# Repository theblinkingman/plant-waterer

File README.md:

# plant-waterer
TDR sensor to water a plant automatically

See https://hackaday.io/project/193184-tdr-soil-moisture-sensor for more details

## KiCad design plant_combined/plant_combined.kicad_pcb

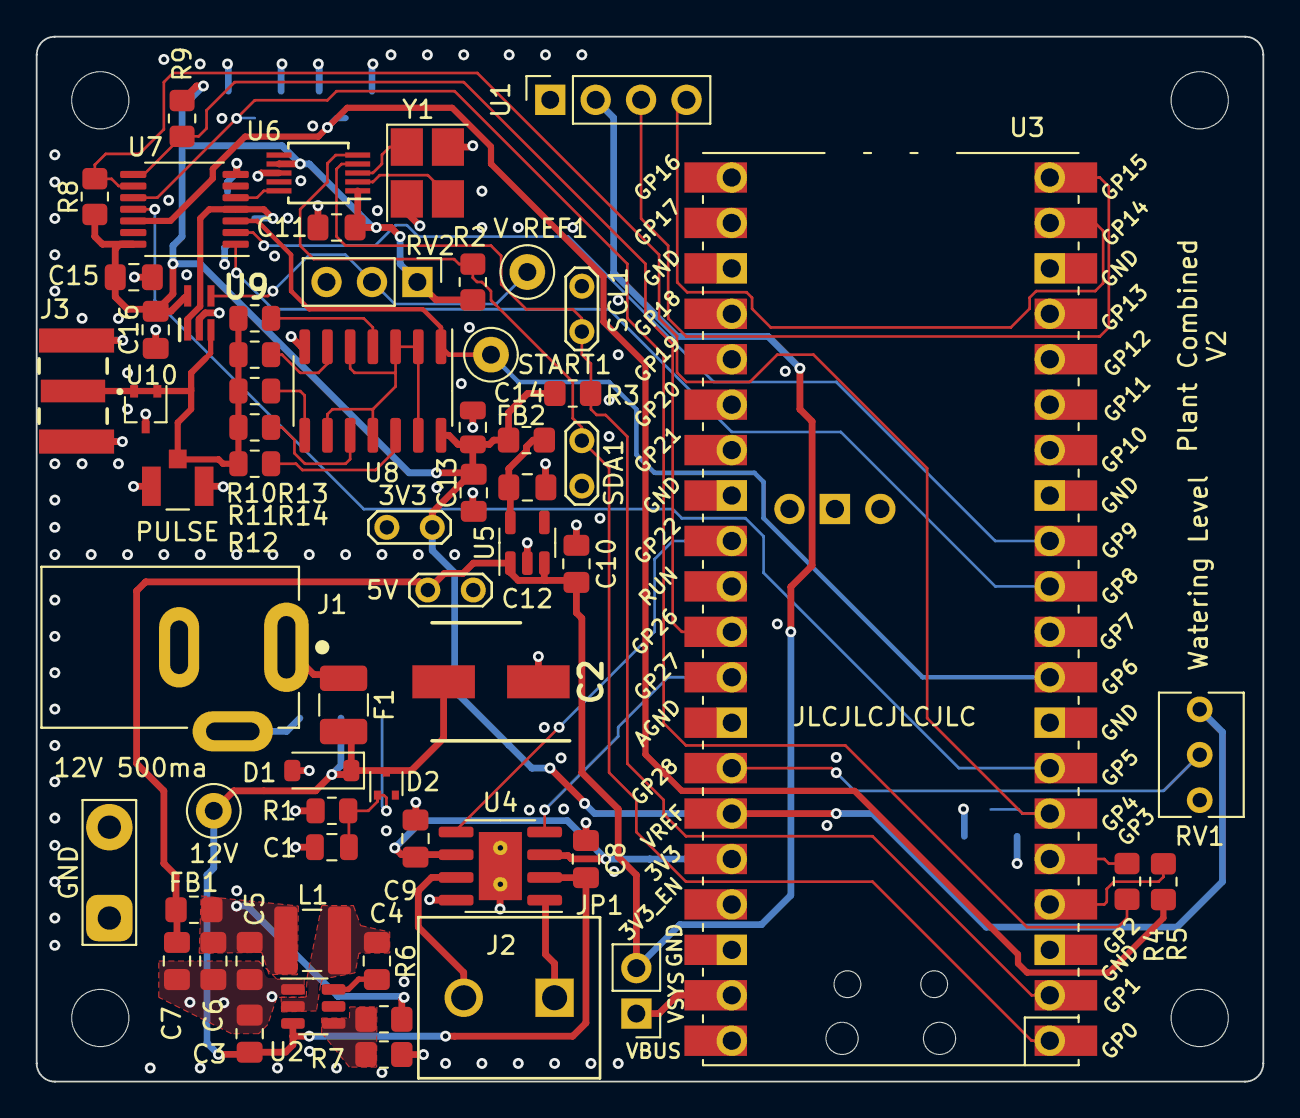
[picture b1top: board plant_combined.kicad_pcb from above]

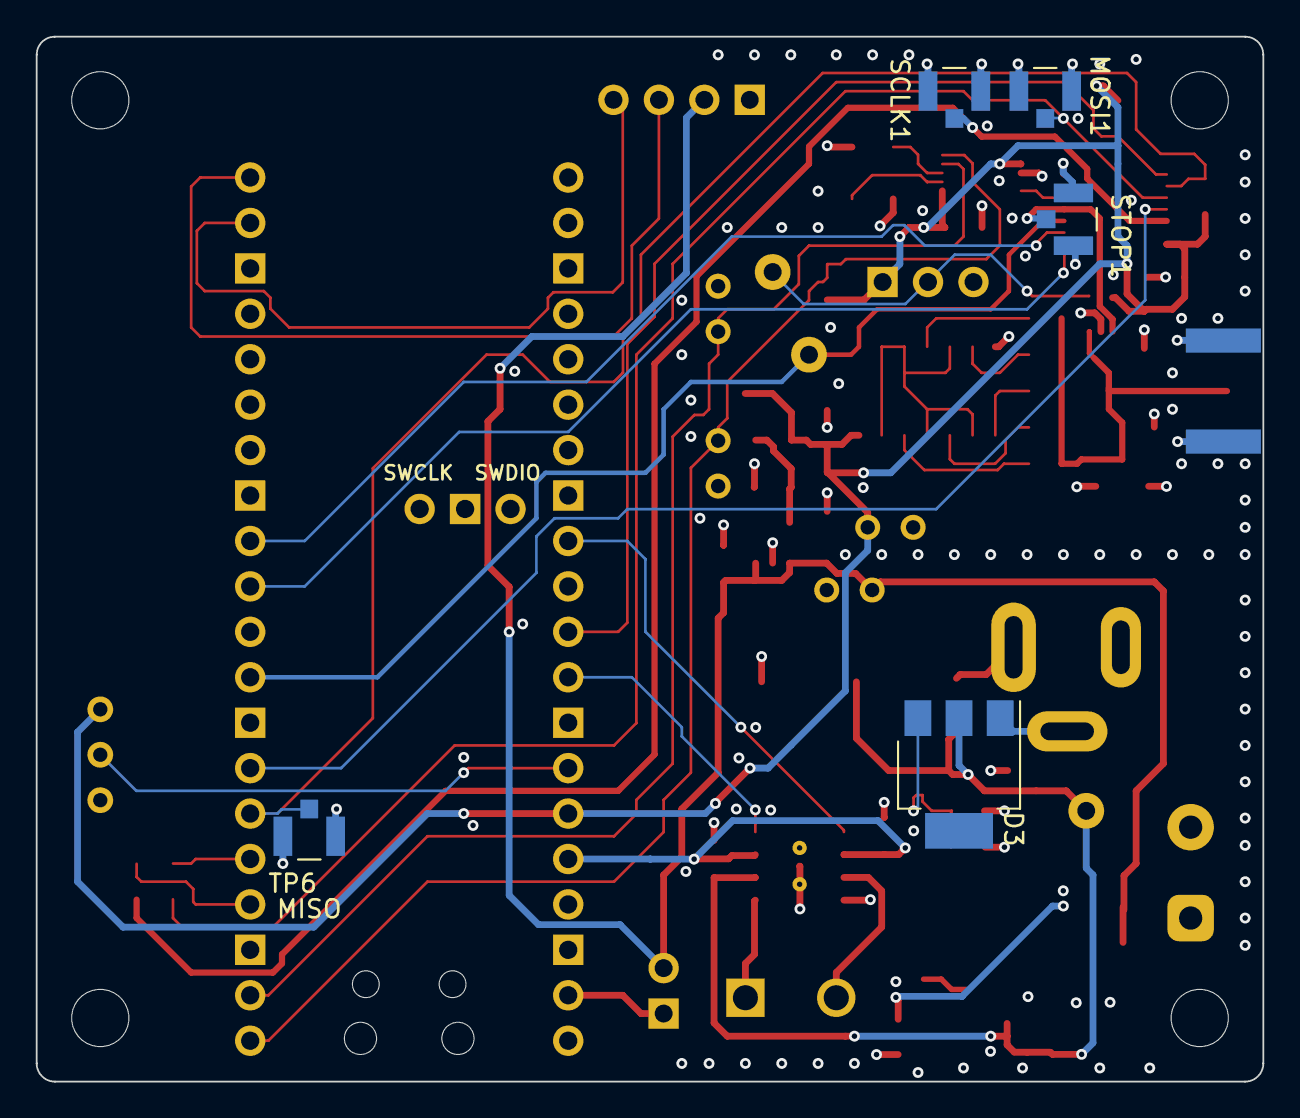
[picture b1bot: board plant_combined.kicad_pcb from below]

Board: 4 copper layers, 68.6 x 58.4 mm, 67 parts (5 on the bottom side), 44 nets.

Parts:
C1: 10nf; C_0805_2012Metric
C2: 100uF; UUA1C101MCL1GS
C3, C8: 10uF; C_0805_2012Metric_Pad1.18x1.45mm_HandSolder
C4: 100nF; C_0805_2012Metric_Pad1.18x1.45mm_HandSolder
C5: 22uF; C_0805_2012Metric_Pad1.18x1.45mm_HandSolder
C6, C7, C9, C10, C11, C12, C13, C15, C16: 1uF; C_0805_2012Metric_Pad1.18x1.45mm_HandSolder
C14: 1uF; C_0805_2012Metric
D1: TV02W480-G; D_SOD-123
D2: BZX84Cxx; SOT-523
D3: BT168GW; SOT-223
F1: 500ma; Fuse_1210_3225Metric_Pad1.42x2.65mm_HandSolder
FB1, FB2: ACML-0805-601-T; R_0805_2012Metric_Pad1.20x1.40mm_HandSolder
J1: PJ-002AH; CUI_PJ-002AH
J2: Conn_01x02; CONN 1x2 5mm
J3: SMA-J-P-H-ST-EM1; SAMTEC_SMA-J-P-H-ST-EM1
JP1: Jumper_2_Bridged; PinHeader_1x02_P2.54mm_Vertical
L1: 4.7uH; SDCL1V4020
MOSI1: TestPoint; HIROSE_U.FL-R-SMT-1(01)
R1: 68; R_0805_2012Metric
R2, R3: 4K7; R_0805_2012Metric_Pad1.20x1.40mm_HandSolder
R4, R5: 82; R_0805_2012Metric_Pad1.20x1.40mm_HandSolder
R6: 52K3; R_0805_2012Metric_Pad1.20x1.40mm_HandSolder
R7, R9: 10K; R_0805_2012Metric_Pad1.20x1.40mm_HandSolder
R8: 1K; R_0805_2012Metric_Pad1.20x1.40mm_HandSolder
R10, R11, R12, R13, R14: 249; R_0805_2012Metric
RV1: R_Potentiometer; Potentiometer_Bourns_3266Y_Vertical
RV2: 10K; PinHeader_1x03_P2.54mm_Vertical
SCL1: TestPoint_2Pole; TestPoint_2Pads_Pitch2.54mm_Drill1mm
SCLK1: TestPoint; HIROSE_U.FL-R-SMT-1(01)
SDA1: TestPoint_2Pole; TestPoint_2Pads_Pitch2.54mm_Drill1mm
START1: TestPoint; TestPoint_Loop_D1.80mm_Drill1.0mm_Beaded
STOP1: TestPoint; HIROSE_U.FL-R-SMT-1(01)
TP1: TestPoint; TestPoint_Loop_D1.80mm_Drill1.0mm_Beaded
TP1#2, TP6: TestPoint; HIROSE_U.FL-R-SMT-1(01)
TP2: TestPoint_2Pole; TestPoint_2Pads_Pitch5.08mm_Drill1.3mm
TP3: TestPoint; TestPoint_2Pads_Pitch2.54mm_Drill1mm
TP4: TestPoint_2Pole; TestPoint_2Pads_Pitch2.54mm_Drill1mm
U1: OLED_DISP; PinSocket_1x04_P2.54mm_Vertical
U2: AP62200WU-7; SOT-23-6
U3: PicoW; RPi_PicoW_SMD_TH
U4: ZXBM5210-SP-13; SOIC-8-1EP_3.9x4.9mm_P1.27mm_EP2.41x3.81mm
U5: MCP1700T; TSOT-23-5
U6: SI5351A-B-GT; MSOP-10_3x3mm_P0.5mm
U7: TDC7200PWR; TSSOP-14_4.4x5mm_P0.65mm
U8: 74AC14SC; SOIC-14_3.9x8.7mm_P1.27mm
U9: ADCMP600BKSZ-R2; SOT65P210X110-5N
U10: ESD7002; SOT-323_SC-70
V REF1: TestPoint; TestPoint_Loop_D1.80mm_Drill1.0mm_Beaded
Y1: Crystal_GND24; Crystal_SMD_3225-4Pin_3.2x2.5mm_HandSoldering

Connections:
+3.3V: C9.2, U3.36 (3V3), U4.3 (VDD), U4.6 (VREF)
+3.3VA: C11.2, C13.2, C14.1, C15.2, C16.2, FB2.2, R2.1, R3.1, R8.2, R9.2, RV1.1, RV2.1, TP4.2, U3.35 (ADC_VREF), U6.1 (VDD), U6.7 (VDDO), U7.14 (VDD), U8.14 (VCC), U9.5 (VCC_I/O)
+5V: C7.2, C10.2, FB1.2, JP1.2 (B), TP3.2, U1.2 (VCC), U5.1 (IN), U5.3 (EN)
+12P: C2.2, C3.2, C8.2, D1.1, D2.3 (K), D3.2 (A), F1.2, TP1.1, U2.3 (VIN), U4.2 (VM)
/5V_JUMP: JP1.1 (A), U3.39 (VSYS)
/5V_UNFILT: C5.2, C6.2, FB1.1, L1.2, R6.1
/AIN1: U3.32 (GPIO27_ADC1), U4.4 (FWD)
/AIN2: U3.29 (GPIO22), U4.5 (REV)
/AO1: J2.1, U4.1 (OUT_1)
/AO2: J2.2, U4.7 (OUT_2)
/FB: R6.2, R7.1, U2.4 (FB)
/SW: C4.1, L1.1, U2.2 (SW)
/VIN: F1.1, J1.1
/tdr_sensor/+3_UNFILTERED: C12.2, FB2.1, U5.5 (OUT)
/tdr_sensor/CLK: U6.10 (CLK0), U7.5 (CLOCK)
/tdr_sensor/PULSE: J3.1, R10.2, R11.2, R12.2, R13.2, R14.2, TP1#2.1, U9.3 (VP), U10.1, U10.2
/tdr_sensor/STOP: STOP1.1, U7.4 (STOP), U9.1 (Q)
/tdr_sensor/V ref: RV2.2, U9.4 (VN), V REF1.1
EN: U3.11 (GPIO8), U7.1 (ENABLE)
GND: C1.2, C2.1, C3.1, C5.1, C6.1, C7.1, C8.1, C9.1, C10.1, C11.1, C12.1, C13.1, C14.2, C15.1, C16.1, D1.2, D3.1 (K), J1.2, J1.3, J3.2_1, J3.2_2, J3.3_1, J3.3_2, MOSI1.2, R1.1, R7.2, RV1.3, RV2.3, SCL1.2, SCLK1.2, SDA1.1, STOP1.2, TP1#2.2, TP2.1, TP2.2, TP3.1, TP4.1, TP6.2, U1.1 (GND), U2.1 (GND), U3.3 (GND), U3.8 (GND), U3.13 (GND), U3.18 (GND), U3.23 (GND), U3.28 (GND), U3.33 (AGND), U3.38 (GND), U4.8 (GND), U4.9 (EP), U5.2 (GND), U6.8 (GND), U7.7 (GND), U8.7 (GND), U9.2 (GND), U10.3, Y1.2, Y1.4
INTB: R9.1, U3.31 (GPIO26_ADC0), U7.8 (INTB)
MISO: R8.1, TP6.1, U3.6 (GPIO4), U7.9 (DOUT)
MOSI: MOSI1.1, R4.2, U7.10 (DIN)
unnamed: C1.1, D2.1 (A), D3.3 (G), R1.2
unnamed: U1.3 (SCK), U3.20 (GPIO15)
unnamed: U1.4 (SDA), U3.19 (GPIO14)
unnamed: C4.2, U2.6 (BST)
unnamed: R5.1, U3.4 (GPIO2)
unnamed: R4.1, U3.5 (GPIO3)
unnamed: RV1.2, U3.34 (GPIO28_ADC2)
unnamed: U6.2 (XA), Y1.3
unnamed: U6.3 (XB), Y1.1
unnamed: U8.2 (O0), U8.3 (I1), U8.5 (I2), U8.9 (I3), U8.11 (I4), U8.13 (I5)
unnamed: R10.1, U8.4 (O1)
unnamed: R11.1, U8.6 (O2)
unnamed: R12.1, U8.8 (O3)
unnamed: R13.1, U8.10 (O4)
unnamed: R14.1, U8.12 (O5)
SCL: R3.2, SCL1.1, U3.2 (GPIO1), U6.4 (SCL)
SCLK: R5.2, SCLK1.1, U7.12 (SCLK)
SDA: R2.2, SDA1.2, U3.1 (GPIO0), U6.5 (SDA)
START: START1.1, U3.9 (GPIO6), U7.3 (START), U8.1 (I0)
TDC CSB: U3.7 (GPIO5), U7.11 (CSB)
TRIG: U3.12 (GPIO9), U7.2 (TRIGG)

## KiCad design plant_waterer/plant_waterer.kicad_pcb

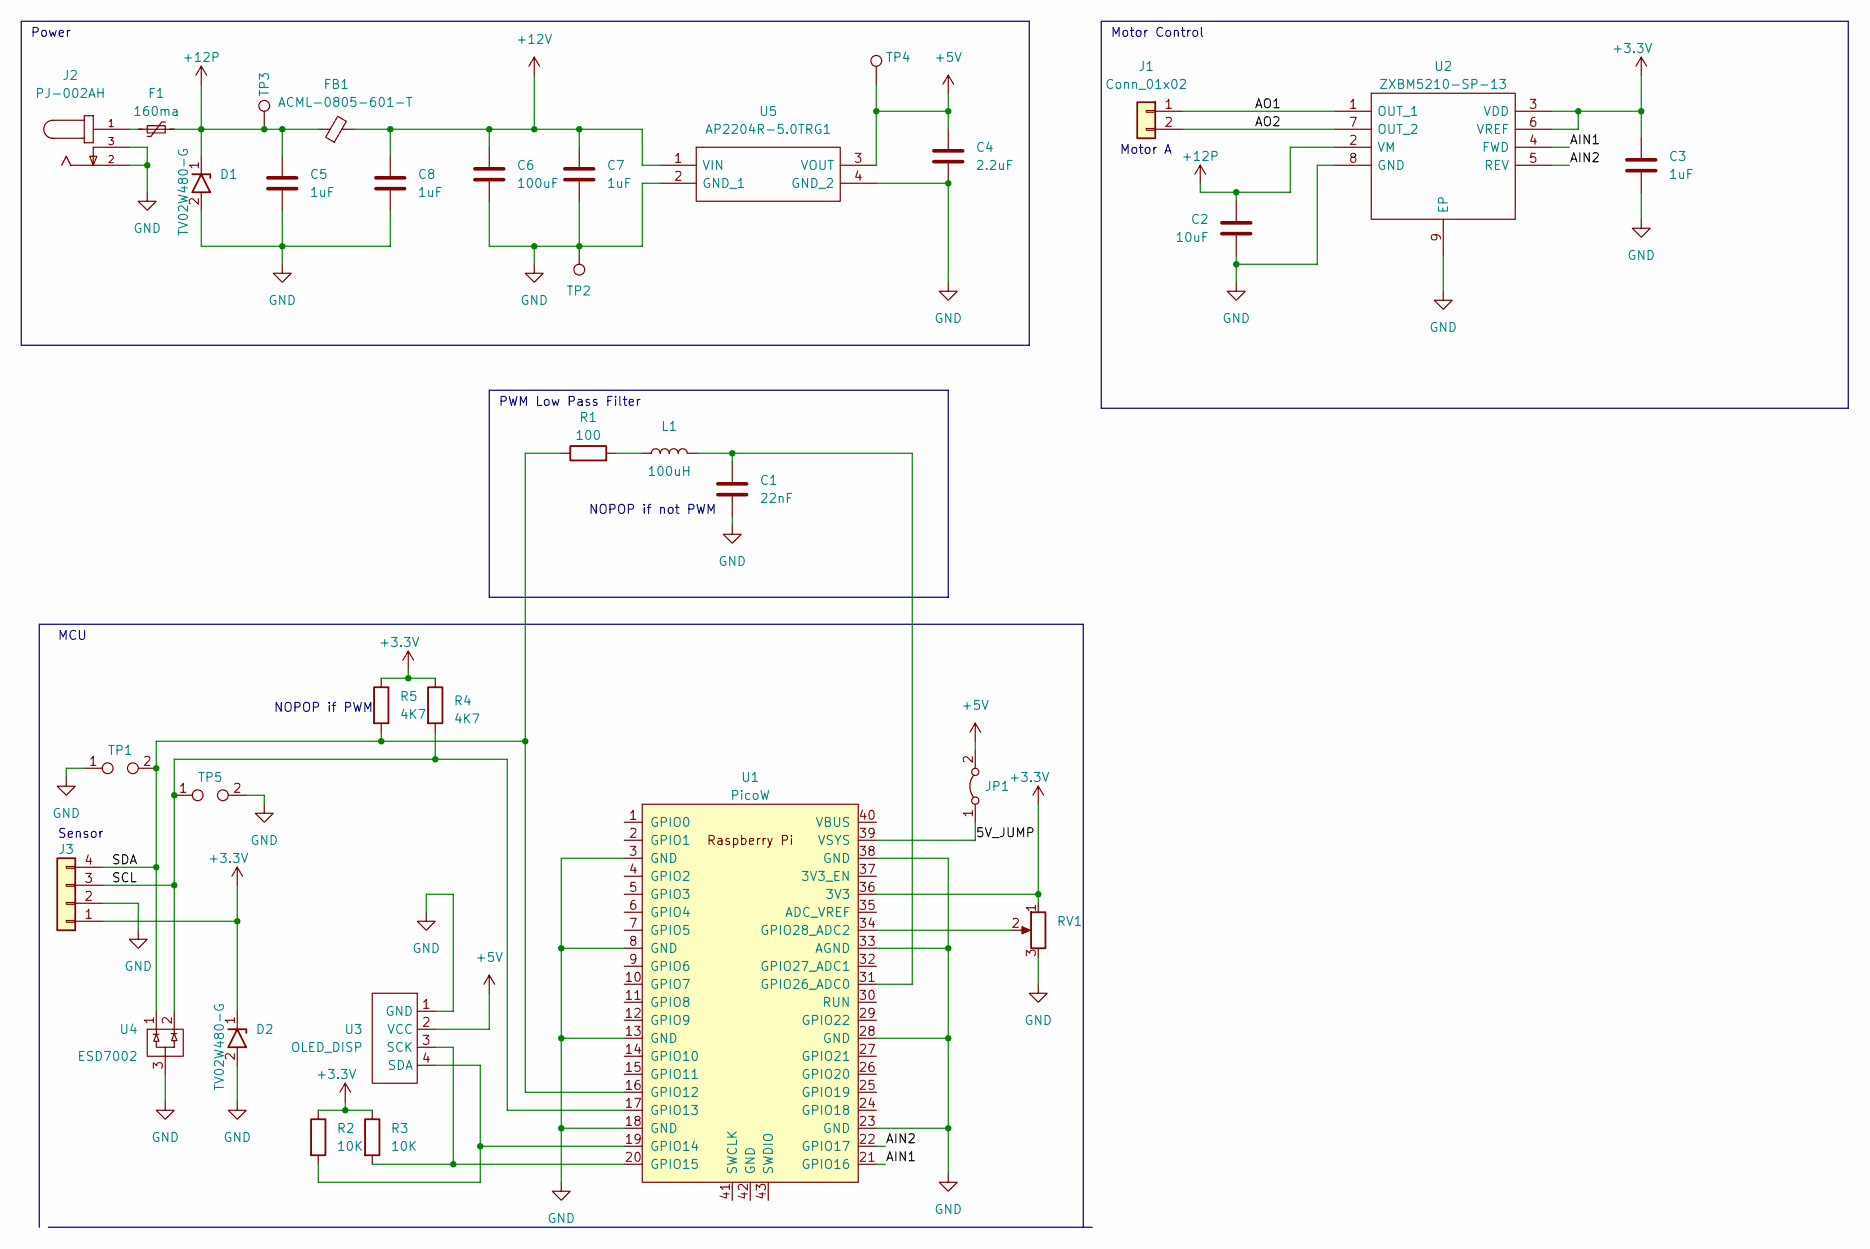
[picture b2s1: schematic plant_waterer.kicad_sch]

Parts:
C1: 22nF; C_0805_2012Metric_Pad1.18x1.45mm_HandSolder
C2: 10uF; C_0805_2012Metric_Pad1.18x1.45mm_HandSolder
C3, C5, C7, C8: 1uF; C_0805_2012Metric_Pad1.18x1.45mm_HandSolder
C4: 2.2uF; C_0805_2012Metric_Pad1.18x1.45mm_HandSolder
C6: 100uF; UUA1C101MCL1GS
D1, D2: TV02W480-G; D_SOD-123
F1: 160ma; Fuse_1210_3225Metric_Pad1.42x2.65mm_HandSolder
FB1: ACML-0805-601-T; R_0805_2012Metric_Pad1.20x1.40mm_HandSolder
J1: Conn_01x02; CONN 1x2 5mm
J2: PJ-002AH; CUI_PJ-002AH
J3: Conn_01x03; PinSocket_1x04_P2.54mm_Vertical
JP1: Jumper_2_Bridged; PinHeader_1x02_P2.54mm_Vertical
L1: 100uH; L_0805_2012Metric_Pad1.05x1.20mm_HandSolder
R1: 100; R_0805_2012Metric_Pad1.20x1.40mm_HandSolder
R2, R3: 10K; R_0805_2012Metric_Pad1.20x1.40mm_HandSolder
R4, R5: 4K7; R_0805_2012Metric_Pad1.20x1.40mm_HandSolder
RV1: R_Potentiometer; Potentiometer_Bourns_3266Y_Vertical
TP1, TP5: TestPoint_2Pole; TestPoint_2Pads_Pitch5.08mm_Drill1.3mm
TP2: TestPoint; TestPoint_2Pads_Pitch5.08mm_Drill1.3mm
TP3, TP4: TestPoint; TestPoint_Loop_D1.80mm_Drill1.0mm_Beaded
U1: PicoW; RPi_PicoW_SMD_TH
U2: ZXBM5210-SP-13; SOIC-8-1EP_3.9x4.9mm_P1.27mm_EP2.41x3.81mm; Manufacturer_Part_Number ZXBM5210-SP-13; Mouser Part Number 621-ZXBM5210-SP-13
U3: OLED_DISP; PinSocket_1x04_P2.54mm_Vertical
U4: ESD7002; SOT-323_SC-70
U5: AP2204R-5.0TRG1; AP2204R50TRG1; Manufacturer_Part_Number AP2204R-5.0TRG1; Mouser Part Number 621-AP2204R-5.0TRG1

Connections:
+3.3V: C3.2, D2.1, J3.1, R2.1, R3.1, R4.1, R5.1, RV1.1, U1.36 (3V3), U2.3 (VDD), U2.6 (VREF)
+5V: C4.2, JP1.2 (B), TP4.1, U3.2 (VCC), U5.3 (VOUT)
+12P: C2.2, C5.2, D1.1, F1.2, FB1.1, TP3.1, U2.2 (VM)
+12V: C6.2, C7.2, C8.2, FB1.2, U5.1 (VIN)
/5V_JUMP: JP1.1 (A), U1.39 (VSYS)
/AIN1: U1.21 (GPIO16), U2.4 (FWD)
/AIN2: U1.22 (GPIO17), U2.5 (REV)
/AO1: J1.1, U2.1 (OUT_1)
/AO2: J1.2, U2.7 (OUT_2)
/SCL: J3.3, R4.2, TP5.1, U1.17 (GPIO13), U4.2
/SDA: J3.4, R1.1, R5.2, TP1.2, U1.16 (GPIO12), U4.1
GND: C1.1, C2.1, C3.1, C4.1, C5.1, C6.1, C7.1, C8.1, D1.2, D2.2, J2.2, J2.3, J3.2, RV1.3, TP1.1, TP2.1, TP5.2, U1.3 (GND), U1.8 (GND), U1.13 (GND), U1.18 (GND), U1.23 (GND), U1.28 (GND), U1.33 (AGND), U1.38 (GND), U2.8 (GND), U2.9 (EP), U3.1 (GND), U4.3, U5.2 (GND_1), U5.4 (GND_2)
unnamed: F1.1, J2.1
unnamed: L1.1, R1.2
unnamed: R2.2, U1.19 (GPIO14), U3.4 (SDA)
unnamed: R3.2, U1.20 (GPIO15), U3.3 (SCK)
unnamed: C1.2, L1.2, U1.31 (GPIO26_ADC0)
unnamed: RV1.2, U1.34 (GPIO28_ADC2)

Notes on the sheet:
Sensor
Motor Control
MCU
Power
NOPOP if not PWM
PWM Low Pass Filter
Motor A
NOPOP if PWM

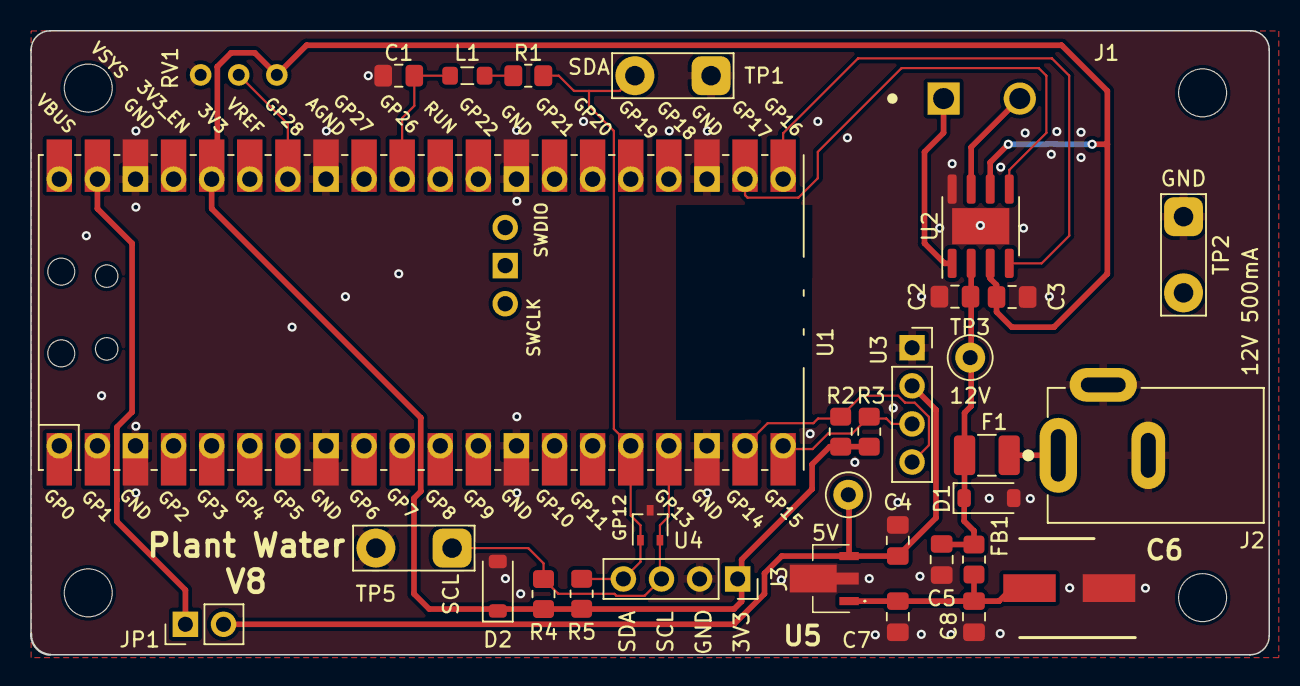
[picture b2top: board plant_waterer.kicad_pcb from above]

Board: 2 copper layers, 82.5 x 41.6 mm, 33 parts (0 on the bottom side), 18 nets.

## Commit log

2022-10-18 Totally custom board
2022-10-18 Code for v3
2022-11-12 Added UART input Added second motor output Added fuse and reverse polarity protection
2022-11-12 Code updates for v3
2022-11-12 Updated version to latest
2022-12-09 Display sensor reading every 10 secs and don't bother with datetime anymore
2022-12-10 Add adjustable level set Add power filtering Add ESD
2022-12-11 Minor clean up and adding schmatic
2023-01-12 Code update for set pot and V7 bodge
2023-01-12 Switched pot to ADC pin
2023-02-20 V7 pre-switch to RPi-Pico
2023-02-21 Swapped in RPi Pico W
2023-02-21 Switched to different motor driver ZXBM5210-SP-13
2023-03-06 Switch code to Pico W and add wifi
2023-03-06 Library for display
2023-03-06 Added off board connectors for I2C
2023-03-06 Cleanup for V5
2023-03-06 Read analog output
2023-03-17 Combined board of both sensor and motor controller
2023-04-02 Code updated to work with combined board
2023-04-02 lib updates
2023-04-02 Fixes for footprints
2023-04-11 Add indicator for recent waterings Fix first watering check
2023-04-12 Added HTTP server with sensor readings Added watchdog
2023-04-15 simple http server logger
2023-05-08 Add logging server
2023-05-08 First attempt to shrink board
2023-05-17 Adding code to handle when the interrupt is missed
2023-05-17 Trying to clean up pulse trace
2023-06-04 Final tweak before release
2023-10-19 Remove settings file again...
2023-11-12 Create LICENCE
2023-11-19 Add pull-up to MISO
2023-11-20 Update code to use faster SPI clock
    20M SPI clock
    Enabled watchdog
    Disabled WiFi
    Removed extra lib
